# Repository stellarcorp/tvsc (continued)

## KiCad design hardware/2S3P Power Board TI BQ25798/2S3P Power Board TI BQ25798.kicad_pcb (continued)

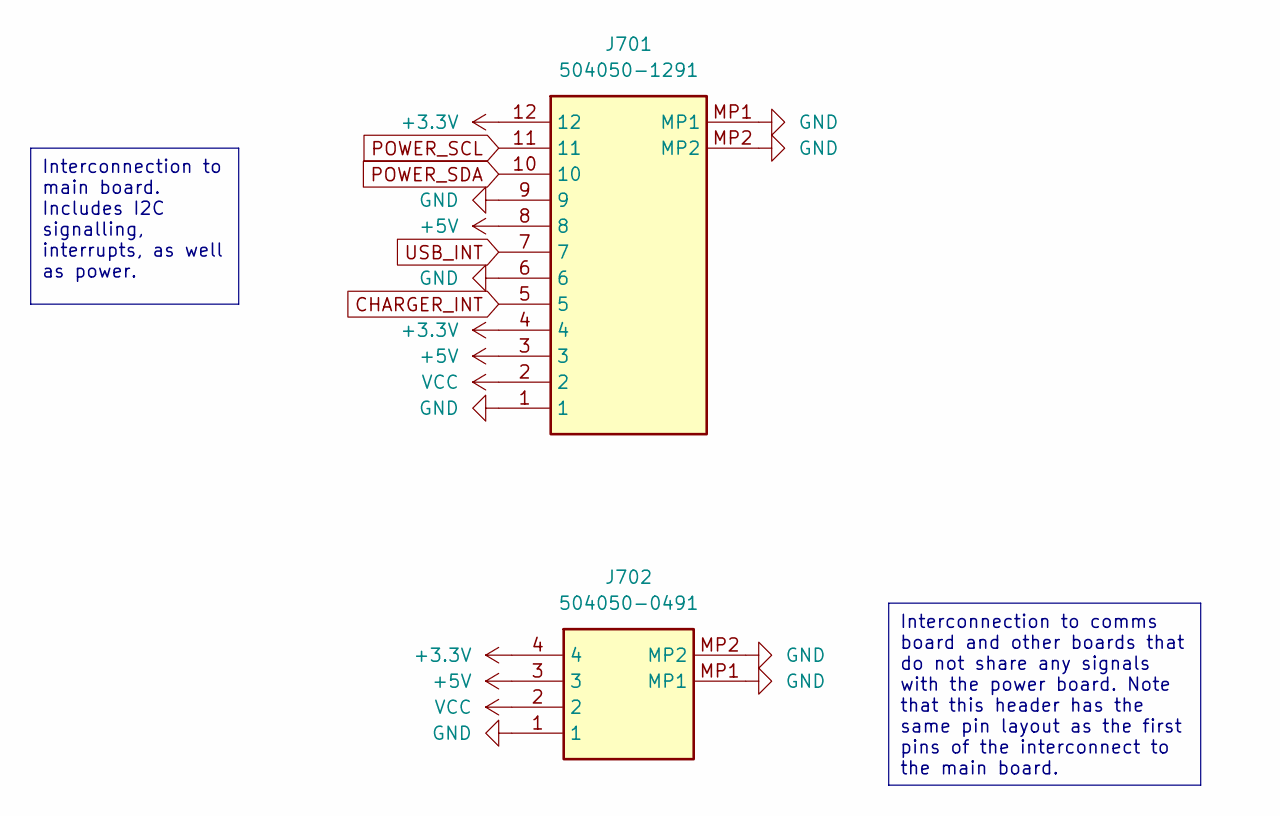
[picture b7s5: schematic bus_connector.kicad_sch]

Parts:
J701: 504050-1291; 5040501291; Manufacturer_Part_Number 504050-1291; Mouser Part Number 538-504050-1291
J702: 504050-0491; 5040500491; Manufacturer_Part_Number 504050-0491; Mouser Part Number 538-504050-0491

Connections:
+3.3V: J701.4, J701.12, J702.4; also elsewhere on the board
+5V: J701.3, J701.8, J702.3; also elsewhere on the board
BATTERY_N: J701.1, J701.6, J701.9, J701.MP1, J701.MP2, J702.1, J702.MP1, J702.MP2; also elsewhere on the board
CHARGER_INT: J701.5; also elsewhere on the board
POWER_SCL: J701.11; also elsewhere on the board
POWER_SDA: J701.10; also elsewhere on the board
USB_INT: J701.7
VCC: J701.2, J702.2; also elsewhere on the board

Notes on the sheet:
Interconnection to main board. Includes I2C signalling, interrupts, as well as power.
Interconnection to comms board and other boards that do not share any signals with the power board. Note that this header has the same pin layout as the first pins of the interconnect to the main board.

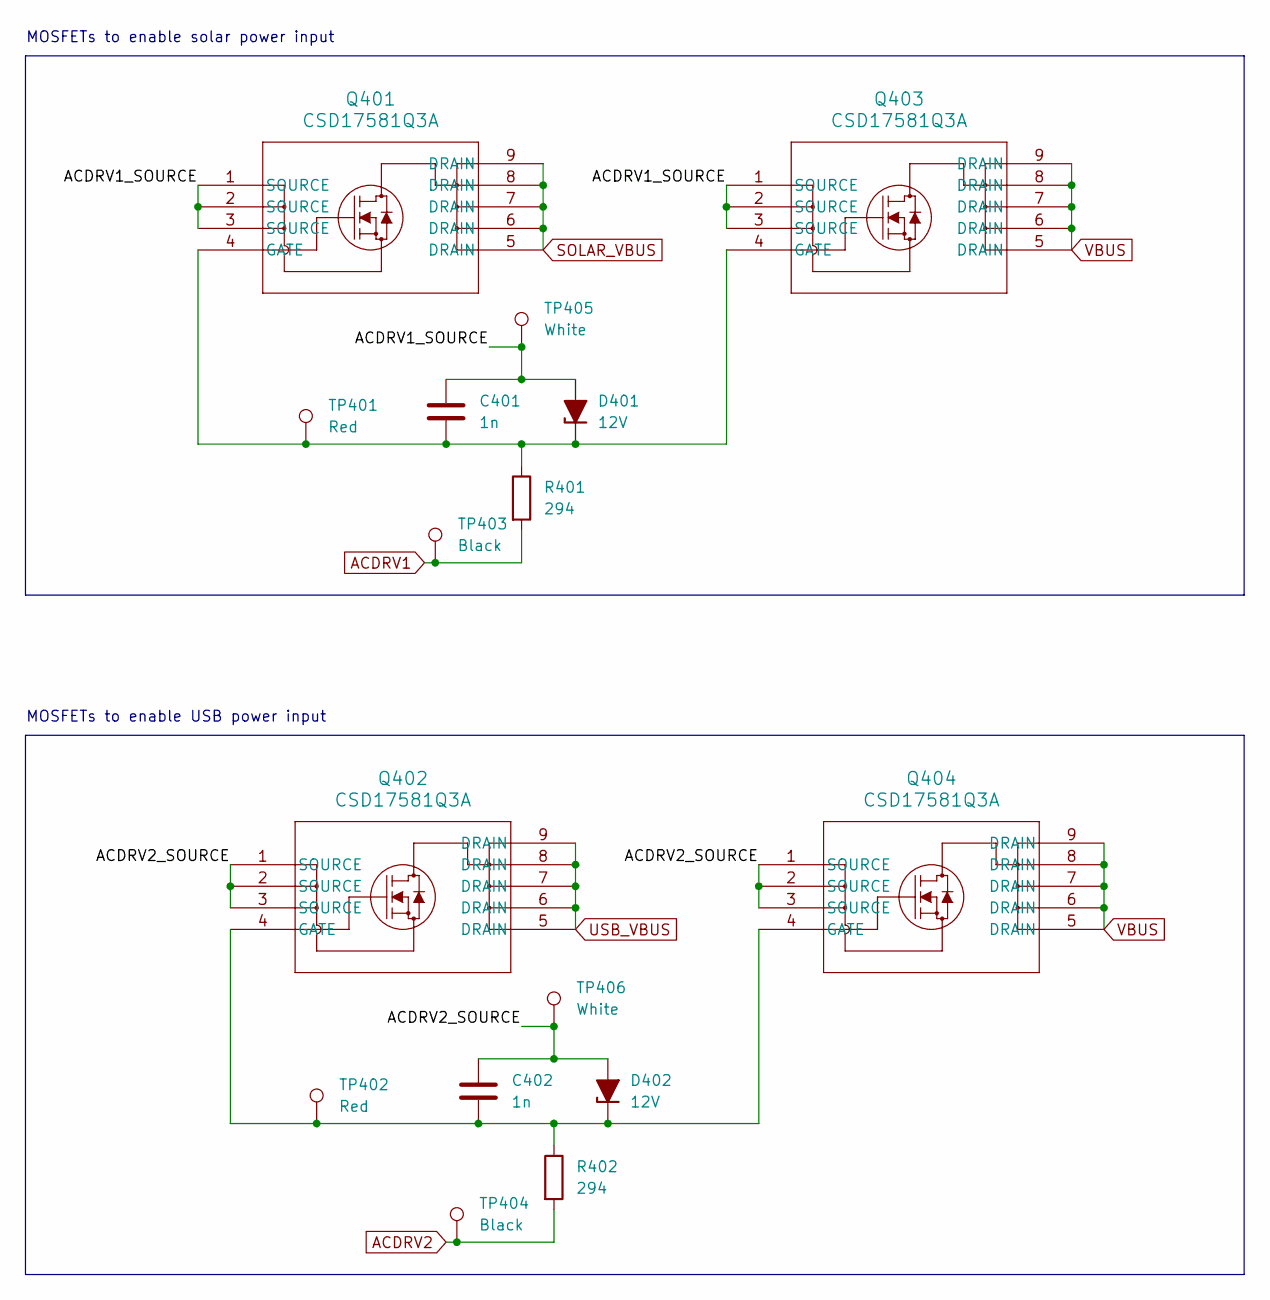
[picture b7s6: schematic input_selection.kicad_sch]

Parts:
C401, C402: 1n; C_0402_1005Metric; Manufacturer Part Number GRM1555C1H102JA01D
D401, D402: 12V; D_SOD-523; Manufacturer Part Number BZT52C12T-7
Q401, Q402, Q403, Q404: CSD17581Q3A; Q3A_TEX; MPN C2866708
R401, R402: 294; R_0603_1608Metric; Manufacturer Part Number RC0603FR-07294RL
TP401, TP402: Red; TestPoint_Keystone_5000-5004_Miniature; MPN C5199900
TP403, TP404: Black; TestPoint_Keystone_5000-5004_Miniature; MPN C238122
TP405, TP406: White; TestPoint_Keystone_5000-5004_Miniature; MPN C238123

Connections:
/Input Selection/ACDRV1_SOURCE: C401.1, D401.2 (A), Q401.1 (SOURCE), Q401.2 (SOURCE), Q401.3 (SOURCE), Q403.1 (SOURCE), Q403.2 (SOURCE), Q403.3 (SOURCE), TP405.1
/Input Selection/ACDRV2_SOURCE: C402.1, D402.2 (A), Q402.1 (SOURCE), Q402.2 (SOURCE), Q402.3 (SOURCE), Q404.1 (SOURCE), Q404.2 (SOURCE), Q404.3 (SOURCE), TP406.1
ACDRV1: R401.2, TP403.1; also elsewhere on the board
ACDRV2: R402.2, TP404.1; also elsewhere on the board
unnamed: C401.2, D401.1 (K), Q401.4 (GATE), Q403.4 (GATE), R401.1, TP401.1
unnamed: C402.2, D402.1 (K), Q402.4 (GATE), Q404.4 (GATE), R402.1, TP402.1
SOLAR_VBUS: Q401.5 (DRAIN), Q401.6 (DRAIN), Q401.7 (DRAIN), Q401.8 (DRAIN), Q401.9 (DRAIN); also elsewhere on the board
USB_VBUS: Q402.5 (DRAIN), Q402.6 (DRAIN), Q402.7 (DRAIN), Q402.8 (DRAIN), Q402.9 (DRAIN); also elsewhere on the board
VBUS: Q403.5 (DRAIN), Q403.6 (DRAIN), Q403.7 (DRAIN), Q403.8 (DRAIN), Q403.9 (DRAIN), Q404.5 (DRAIN), Q404.6 (DRAIN), Q404.7 (DRAIN), Q404.8 (DRAIN), Q404.9 (DRAIN); also elsewhere on the board

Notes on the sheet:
MOSFETs to enable USB power input
MOSFETs to enable solar power input

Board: 4 copper layers, 108 parts (0 on the bottom side), 47 nets, no tracks yet.

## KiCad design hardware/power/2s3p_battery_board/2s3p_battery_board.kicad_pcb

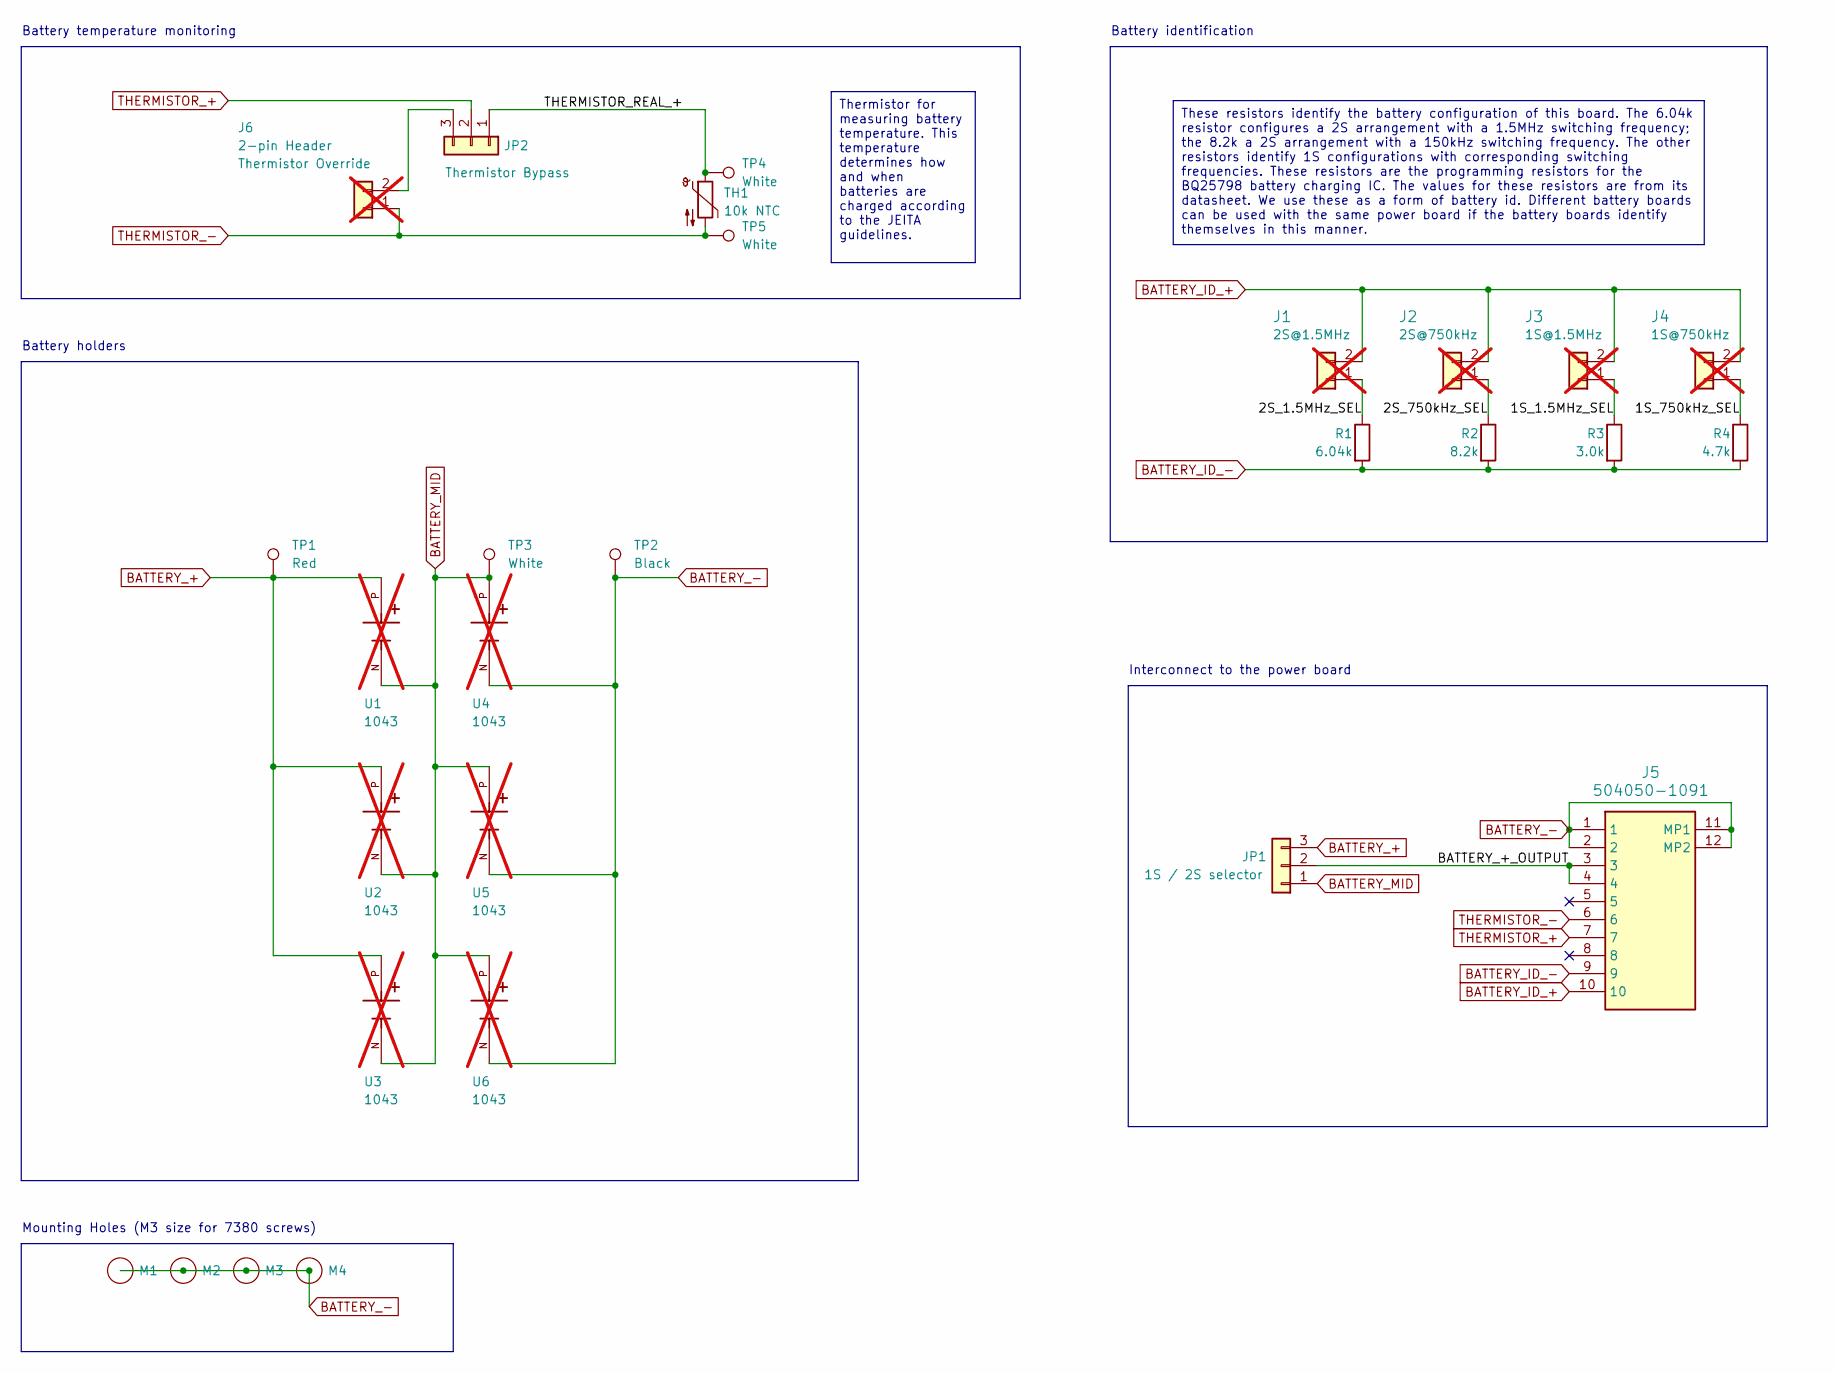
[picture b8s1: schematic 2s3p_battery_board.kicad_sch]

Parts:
J1, J2, J3, J4: 2-pin Header; PinHeader_1x02_P1.27mm_Vertical; Manufacturer Part Number B02B-XASK-1(LF)(SN); not fitted
J5: 504050-1091; MPN C5375652; Mouser Part Number 538-504050-1091
J6: 2-pin Header; PinHeader_1x02_P1.27mm_Vertical; MPN C263753; not fitted
JP1, JP2: Conn_01x03; HDRV3W64P0X254_1X3_762X254X869P; MPN C2915006; Mouser Part Number 710-61300311121
M1, M2, M3, M4: MountingHole_3.2mm_M3_ISO7380_Pad_TopBottom
R1: 6.04k; R_0603_1608Metric; MPN C114631
R2: 8.2k; R_0603_1608Metric; MPN C114637
R3: 3.0k; R_0603_1608Metric
R4: 4.7k; R_0603_1608Metric
TH1: 10k NTC; R_0402_1005Metric; MPN C336815
TP1: Red; Keystone_5000; MPN C5199900
TP2: Black; Keystone_5000; MPN C238122
TP3, TP4, TP5: White; Keystone_5002; MPN C238123
U1, U2, U3, U4, U5, U6: 1043; BAT_1043; Manufacturer Part Number 1043; not fitted

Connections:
/1S_1.5MHz_SEL: J3.1, R3.1
/1S_750kHz_SEL: J4.1, R4.1
/2S_1.5MHz_SEL: J1.1, R1.1
/2S_750kHz_SEL: J2.1, R2.1
/BATTERY_+_OUTPUT: J5.3, J5.4, JP1.2
/THERMISTOR_REAL_+: JP2.1, TH1.1, TP4.1
BATTERY_+: JP1.3, TP1.1, U1.P, U2.P, U3.P
BATTERY_-: J5.1, J5.2, J5.11 (MP1), J5.12 (MP2), M1.1 (Hole), M2.1 (Hole), M3.1 (Hole), M4.1 (Hole), TP2.1, U4.N, U5.N, U6.N
BATTERY_ID_+: J1.2, J2.2, J3.2, J4.2, J5.10
BATTERY_ID_-: J5.9, R1.2, R2.2, R3.2, R4.2
BATTERY_MID: JP1.1, TP3.1, U1.N, U2.N, U3.N, U4.P, U5.P, U6.P
unnamed: J6.2, JP2.3
THERMISTOR_+: J5.7, JP2.2
THERMISTOR_-: J5.6, J6.1, TH1.2, TP5.1

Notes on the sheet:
Thermistor for measuring battery temperature. This temperature determines how and when batteries are charged according to the JEITA guidelines.
These resistors identify the battery configuration of this board. The 6.04k resistor configures a 2S arrangement with a 1.5MHz switching frequency; the 8.2k a 2S arrangement with a 150kHz switching frequency. The other resistors identify 1S configurations with corresponding switching frequencies. T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
Mounting Holes (M3 size for 7380 screws)
Battery identification
Battery temperature monitoring
Battery holders
Interconnect to the power board

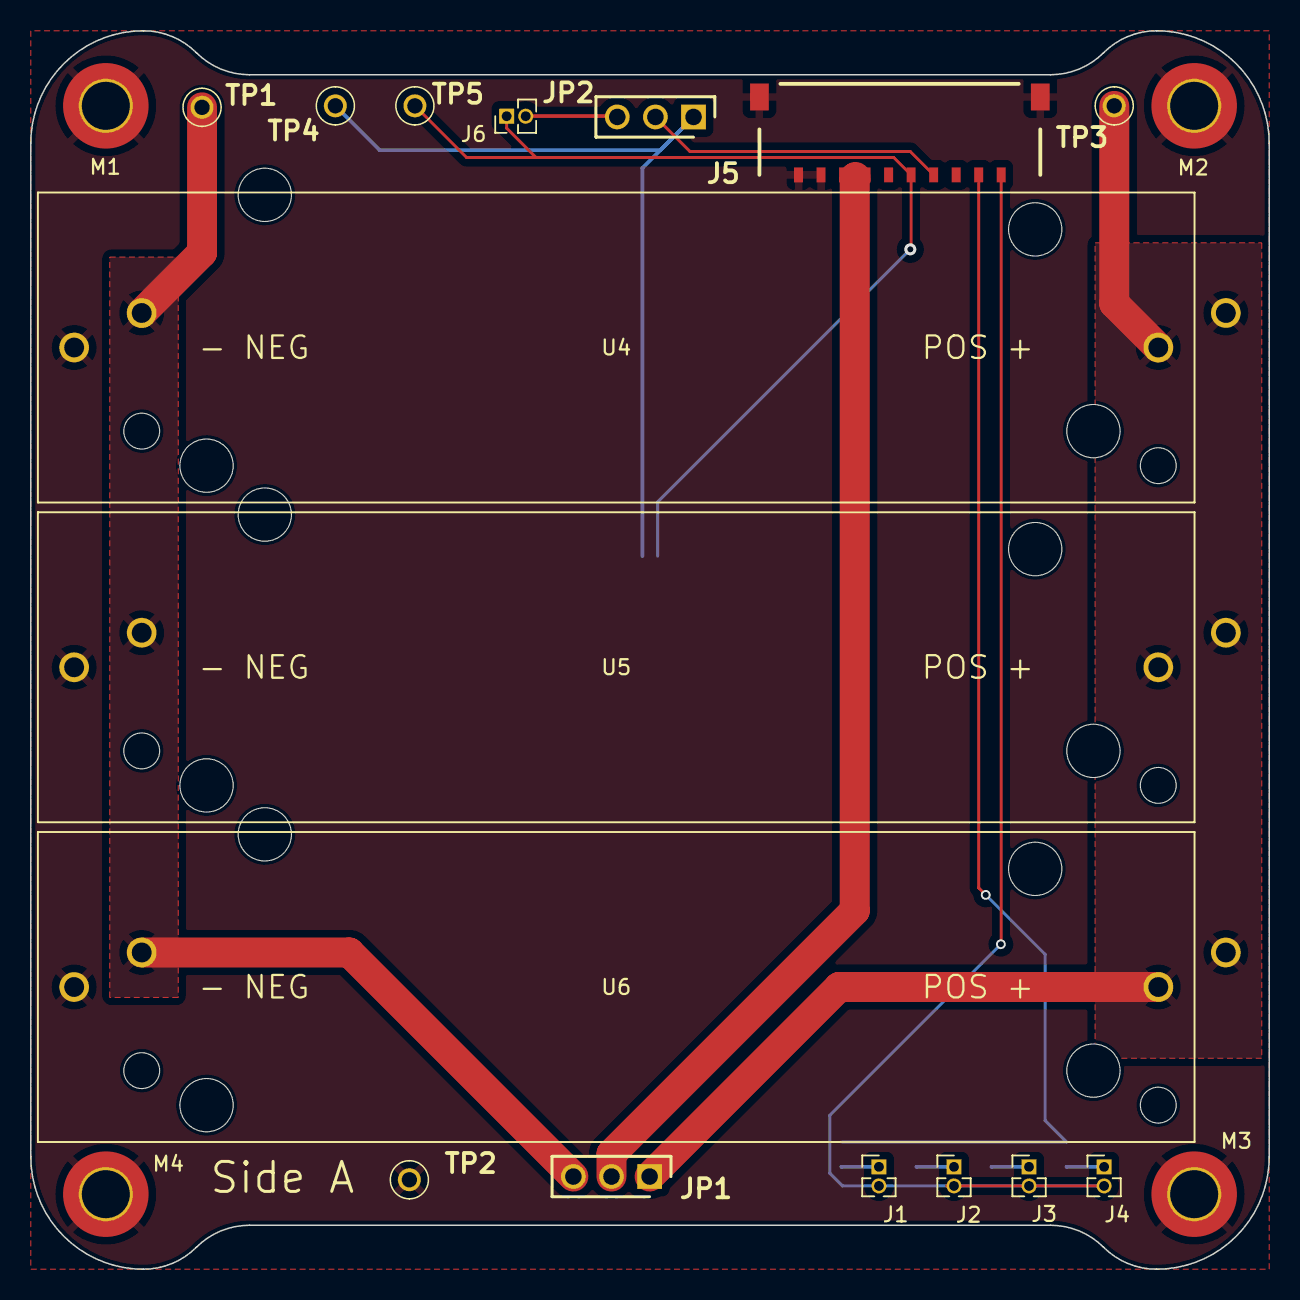
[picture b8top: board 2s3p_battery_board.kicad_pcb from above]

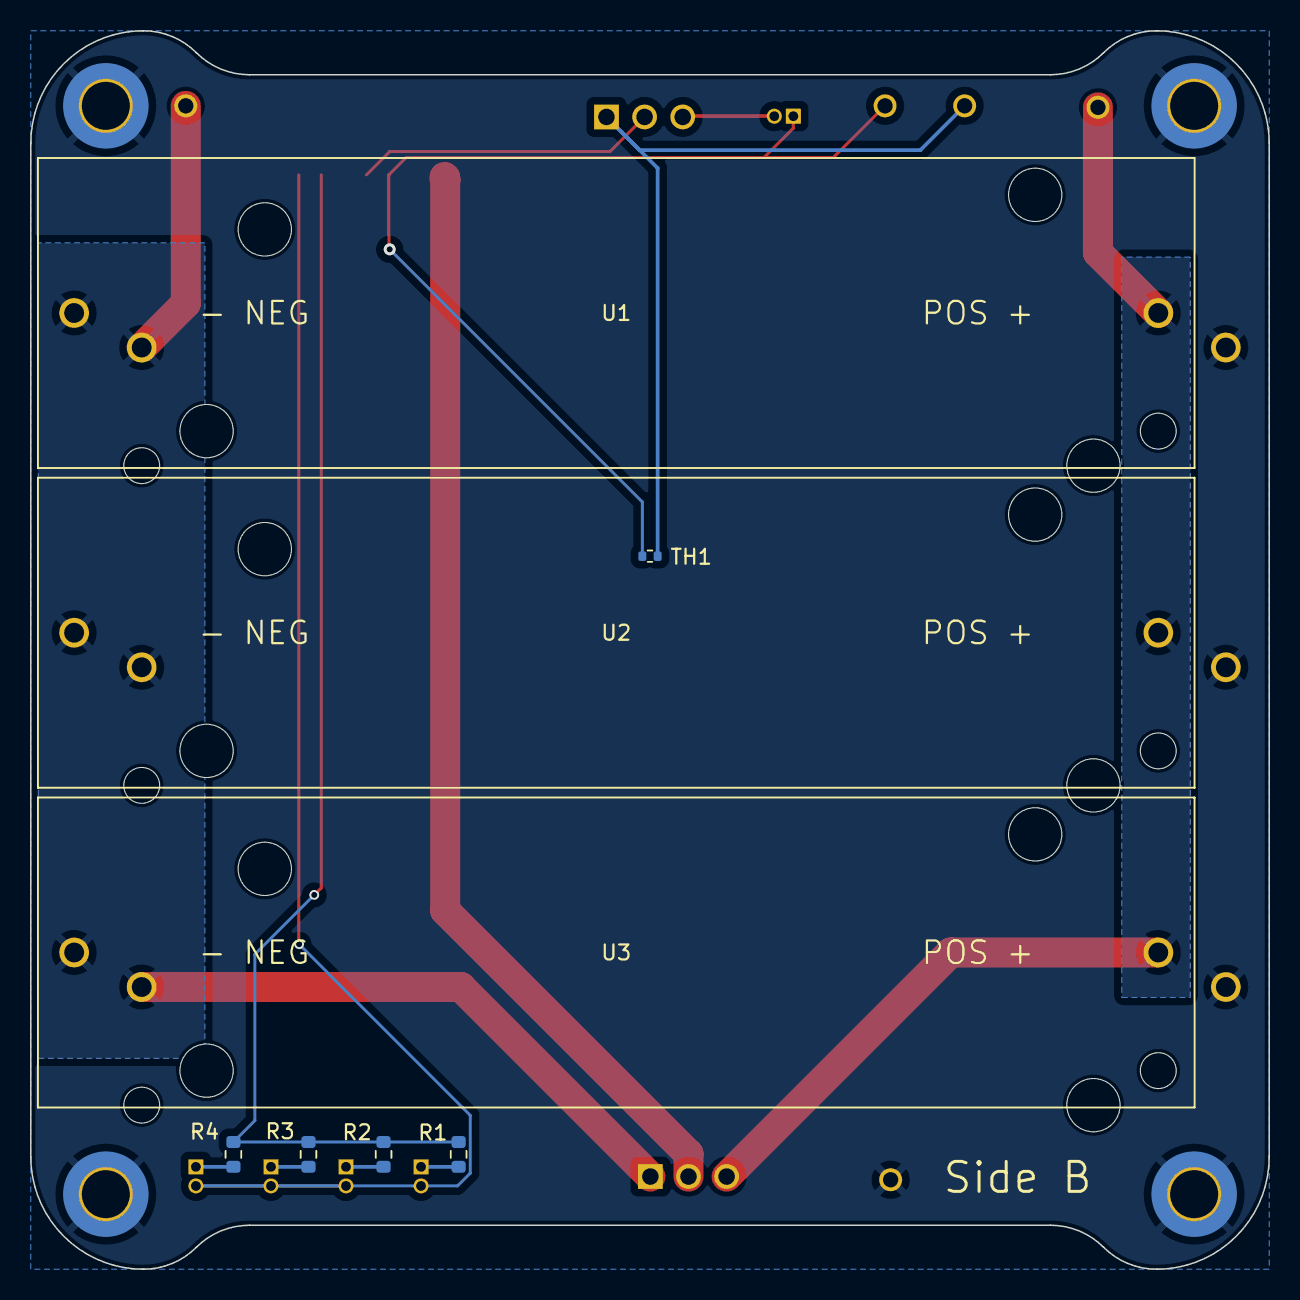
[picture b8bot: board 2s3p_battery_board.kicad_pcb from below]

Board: 2 copper layers, 82.5 x 82.5 mm, 28 parts (8 on the bottom side), 14 nets.

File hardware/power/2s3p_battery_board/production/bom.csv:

Designator,Footprint,Quantity,Value,LCSC Part #
J5,504050-1091,1,504050-1091,C5375652
"JP1, JP2",HDRV3W64P0X254_1X3_762X254X869P,2,Conn_01x03,C2915006
R1,0603,1,6.04k,C114631
R2,0603,1,8.2k,C114637
R3,0603,1,3.0k,C126358
R4,0603,1,4.7k,C99782
TH1,0402,1,10k NTC,C336815
TP1,Keystone_5000,1,Red,C5199900
TP2,Keystone_5000,1,Black,C238122
"TP3, TP4, TP5",Keystone_5002,3,White,C238123
